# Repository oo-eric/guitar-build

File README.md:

# MIDI Guitar Build

A DIY guitar that doubles as a polyphonic MIDI controller. Six individual
single-string pickups feed a Teensy 4.0, which converts each string's vibration
into MIDI in real time — pitch, note on/off, and per-string pitch bend — using
the MPE (MIDI Polyphonic Expression) standard so every string lives on its own
channel and bends independently.

It's a _hybrid_ instrument: alongside the six hex pickups there's one standard
magnetic pickup, so it still plays and sounds like a normal guitar through an amp
while the digital side drives synths.

The electronics don't live in the guitar. The body carries pickups and a single
**13-pin (Roland GK standard) socket**; everything else — preamp, Teensy, MIDI
OUT, jacks — lives in a stompbox on the floor. The guitar end is entirely
passive.

## Status

**Phase 2 — 6-string expansion (in progress).**

- **Phase 1 (complete):** single-string proof of concept — pickup → buffer → ADC
  → onset detection → YIN pitch detection → MPE MIDI, end-to-end into a DAW.
- **Phase 2 (current):** modular firmware now runs all six strings. Single string
  is working end-to-end on the MCP6002 buffer (no battery); threshold calibration
  and per-string gain in progress. The **HexScope** app shows every string live
  on an iPhone, iPad or Mac, for checking wiring and comparing changes.
- **Phase 3 (started):** body and neck arrived 2026-08-08; the hex pickups are
  wired to the guitar's 13-pin socket but not yet connected to the preamp.
  Stomp box enclosure still to come. PCB designed and DRC-clean, waiting on a
  cable test before fabrication.
- **Future exploration:** an MPU-6050 accelerometer/gyro on the body or neck to
  turn physical gestures (tilt, shake, orientation) into MIDI CC.

See [`docs/plan.md`](docs/plan.md) for the full phased plan and parts list.

## Signal chain

```mermaid
flowchart LR
    subgraph G["Guitar (passive)"]
        S["Guitar string"] --> P["77HC hex pickup<br>×6"]
        M["Porter magnetic<br>pickup"]
        SW["Mode switch<br>Guitar / Mix / MIDI"]
        GJ["Guitar 1/4&quot; jack<br>(switched)"]
        M --> SW --> GJ
    end
    P --> K["13-pin GK cable<br>hex 1-6, magnetic 7, MIDI on/off 10"]
    GJ -- "no plug in" --> K
    SW -- "MIDI on/off" --> K
    subgraph BOX["Stomp box"]
        B["MCP6002 preamp<br>6ch, 46x, 3.3V from Teensy"]
        ADC["Teensy 4.0<br>A0-A5"]
        DSP["Onset → YIN pitch<br>→ MPE MIDI"]
        B --> ADC --> DSP
    end
    K --> B
    K --> J["1/4&quot; jack<br>(passive passthrough)"]
    DSP --> DIN["MIDI OUT<br>5-pin DIN"]
    DSP --> USB["USB-C"]
    GJ -- "plug in" --> AMP
    DIN --> SY["Hardware synth<br>(stage)"]
    USB --> C["Computer / DAW<br>(desk)"]
    J --> AMP["Amp"]
```

## Hardware

- **Teensy 4.0** — 600MHz ARM Cortex-M7, dual 12-bit ADC, built-in USB MIDI
- **Ubertar 77HC** single-string ("hexaphonic") pickups ×6
- **MCP6002** rail-to-rail op-amps ×3 (dual channel each = 6 buffer/gain stages),
  running on 3.3V from the Teensy — replaced the original TL072 + 9V battery
- **Porter Pickups** Filtertron-sized humbucker (neck), Boise-made. Goes out the
  guitar's own 1/4" jack when a plug is in it, otherwise down 13-pin pin 7 to the
  stomp box's jack. Wiring of record: [`docs/guitar_wiring.md`](docs/guitar_wiring.md)
- **Custom PCB** — 82 × 156 mm, 2-layer, all through-hole. Generated from
  scripts, not hand-drawn; see `hardware/` and `scripts/`
- Breadboard prototype today; the board is designed but not yet fabricated

Circuit of record: [`docs/buffer_circuit.md`](docs/buffer_circuit.md).
Stomp box design: [`docs/stompbox/`](docs/stompbox/README.md).

## Firmware

Arduino IDE + Teensyduino. Under `firmware/`:

- **`firmware/adc_test/`** — Phase 1 single-string sketch. Uses the Teensy Audio
  library + USB Audio for monitoring; YIN pitch detection.
- **`firmware/experiments/`** — sketches that are **not** part of the MIDI signal
  chain and aren't headed for the pedal. Currently the ILI9341 waveform display,
  parked as a bench tool. Its README records why.
- **`firmware/guitar_midi/`** — Phase 2 modular 6-string firmware. MIDI only
  (no USB Audio). Components:
  - `config.h` — all tunable constants (thresholds, sample rate, MIDI, per-string)
  - `adc_sampler.h/.cpp` — timer-driven 20kHz ADC sampling, 6 channels, per-channel ring buffers
  - `onset_detector.h/.cpp` — RMS-based per-string note on/off state machine
  - `pitch_detector.h/.cpp` — YIN pitch detection with hysteresis
  - `midi_output.h/.cpp` — MPE MIDI output with per-channel pitch bend tracking
  - `telemetry.h/.cpp` — per-string diagnostics sent as USB MIDI SysEx, for HexScope
  - `guitar_midi.ino` — orchestrator with staggered per-string pitch detection

### Flashing

1. Open the sketch in the Arduino IDE with Teensyduino installed.
2. Select **Tools → Board → Teensy 4.0**.
3. Set **Tools → USB Type → "Serial + MIDI"** (Phase 2). The Phase 1 `adc_test`
   sketch uses **"Serial + MIDI + Audio"**.
4. Upload. The Teensy enumerates as a USB MIDI device — add it as an MPE
   instrument in your DAW.

> **Apple Silicon without Rosetta** (macOS 27): use Teensyduino **1.62 or
> later**, which ships a native compiler. Arduino's bundled `ctags` is still
> Intel-only and breaks the `.ino` preprocessing step; see `AGENTS.md` for the
> current workaround.

> **Power note:** don't power the Teensy via VIN and USB at the same time without
> cutting the VIN-VUSB trace.

## Tooling

- **[`app/HexScope/`](app/HexScope/README.md)** — SwiftUI app for iPhone, iPad
  and Mac. Plug the Teensy into the phone and see each string's level, bias,
  pitch and waveform, with warnings for clipping, bad bias and swapped wires.
  Records captures you can compare before and after a change. It reads USB MIDI,
  because iOS can't open the Teensy's serial port.
- `scripts/teensy_serial.py` — serial reader for the Teensy CDC port
- `scripts/guitar_monitor.py` — terminal dashboard of onset / pitch output
- `scripts/gen_body_template.py`, `headstock_layout.py`, `headstock_preview.py`
  — body outline and headstock templates

## Repository layout

```text
firmware/        Teensy sketches
  adc_test/        Phase 1 single-string
  guitar_midi/     Phase 2 modular 6-string (the real one)
  experiments/     parked, not in the signal chain
app/HexScope/    iPhone / iPad / Mac diagnostics app (xcodegen project)
hardware/        KiCad schematic + PCB — GENERATED, do not hand-edit
docs/            build plan, hardware references, circuit + design notes
  stompbox/        enclosure: power, controls, pin map, prior art
scripts/         KiCad and template generators + host-side serial/debug tools
body/            body outline and headstock (OpenSCAD, printable template)
enclosure/       OpenSCAD models (pickup enclosure)
brainstorm/      concept sketches
output/          captured stage notes / logs
AGENTS.md        project instructions for the agent harness
```

`hardware/` is generated by `scripts/gen_kicad_schematic.py` and
`scripts/gen_kicad_pcb.py`. Regenerate in order — schematic →
`check_kicad_netlist.py` → PCB — and never hand-edit the KiCad files.

## Documentation

| Doc                                                              | What's in it                                                     |
| ---------------------------------------------------------------- | ---------------------------------------------------------------- |
| [`docs/plan.md`](docs/plan.md)                                   | Phased build plan, parts list, signal chain, technical notes     |
| [`docs/guitar_build.md`](docs/guitar_build.md)                   | Physical build specs and decisions                               |
| [`docs/guitar_wiring.md`](docs/guitar_wiring.md)                 | **Guitar wiring of record** — jacks, mode switch, grounding      |
| [`docs/guitar_wiring_diagram.md`](docs/guitar_wiring_diagram.md) | Bench sheet: diagram, wire list, meter and continuity checks     |
| [`docs/body_shape.md`](docs/body_shape.md)                       | Body outline design (Jazzmaster × Iceman hybrid)                 |
| [`docs/wood_comparison.md`](docs/wood_comparison.md)             | Body / neck / fretboard tonewood comparison                      |
| [`docs/pickup_selection.md`](docs/pickup_selection.md)           | Standard magnetic pickup selection (Porter Pickups)              |
| [`docs/buffer_circuit.md`](docs/buffer_circuit.md)               | **Circuit of record** — schematic, values, BOM, bring-up         |
| [`docs/stompbox/`](docs/stompbox/README.md)                      | Stomp box: I/O, power, controls, Teensy pin map, prior art       |
| [`docs/wip.md`](docs/wip.md)                                     | ⚠️ Historical Phase-1 breadboard wiring (TL072 + 9V). Superseded |
| [`docs/teensy-4.0.md`](docs/teensy-4.0.md)                       | Teensy 4.0 pinout / reference                                    |
| [`docs/ubertar-77hc-pickup.md`](docs/ubertar-77hc-pickup.md)     | Ubertar 77HC pickup reference                                    |

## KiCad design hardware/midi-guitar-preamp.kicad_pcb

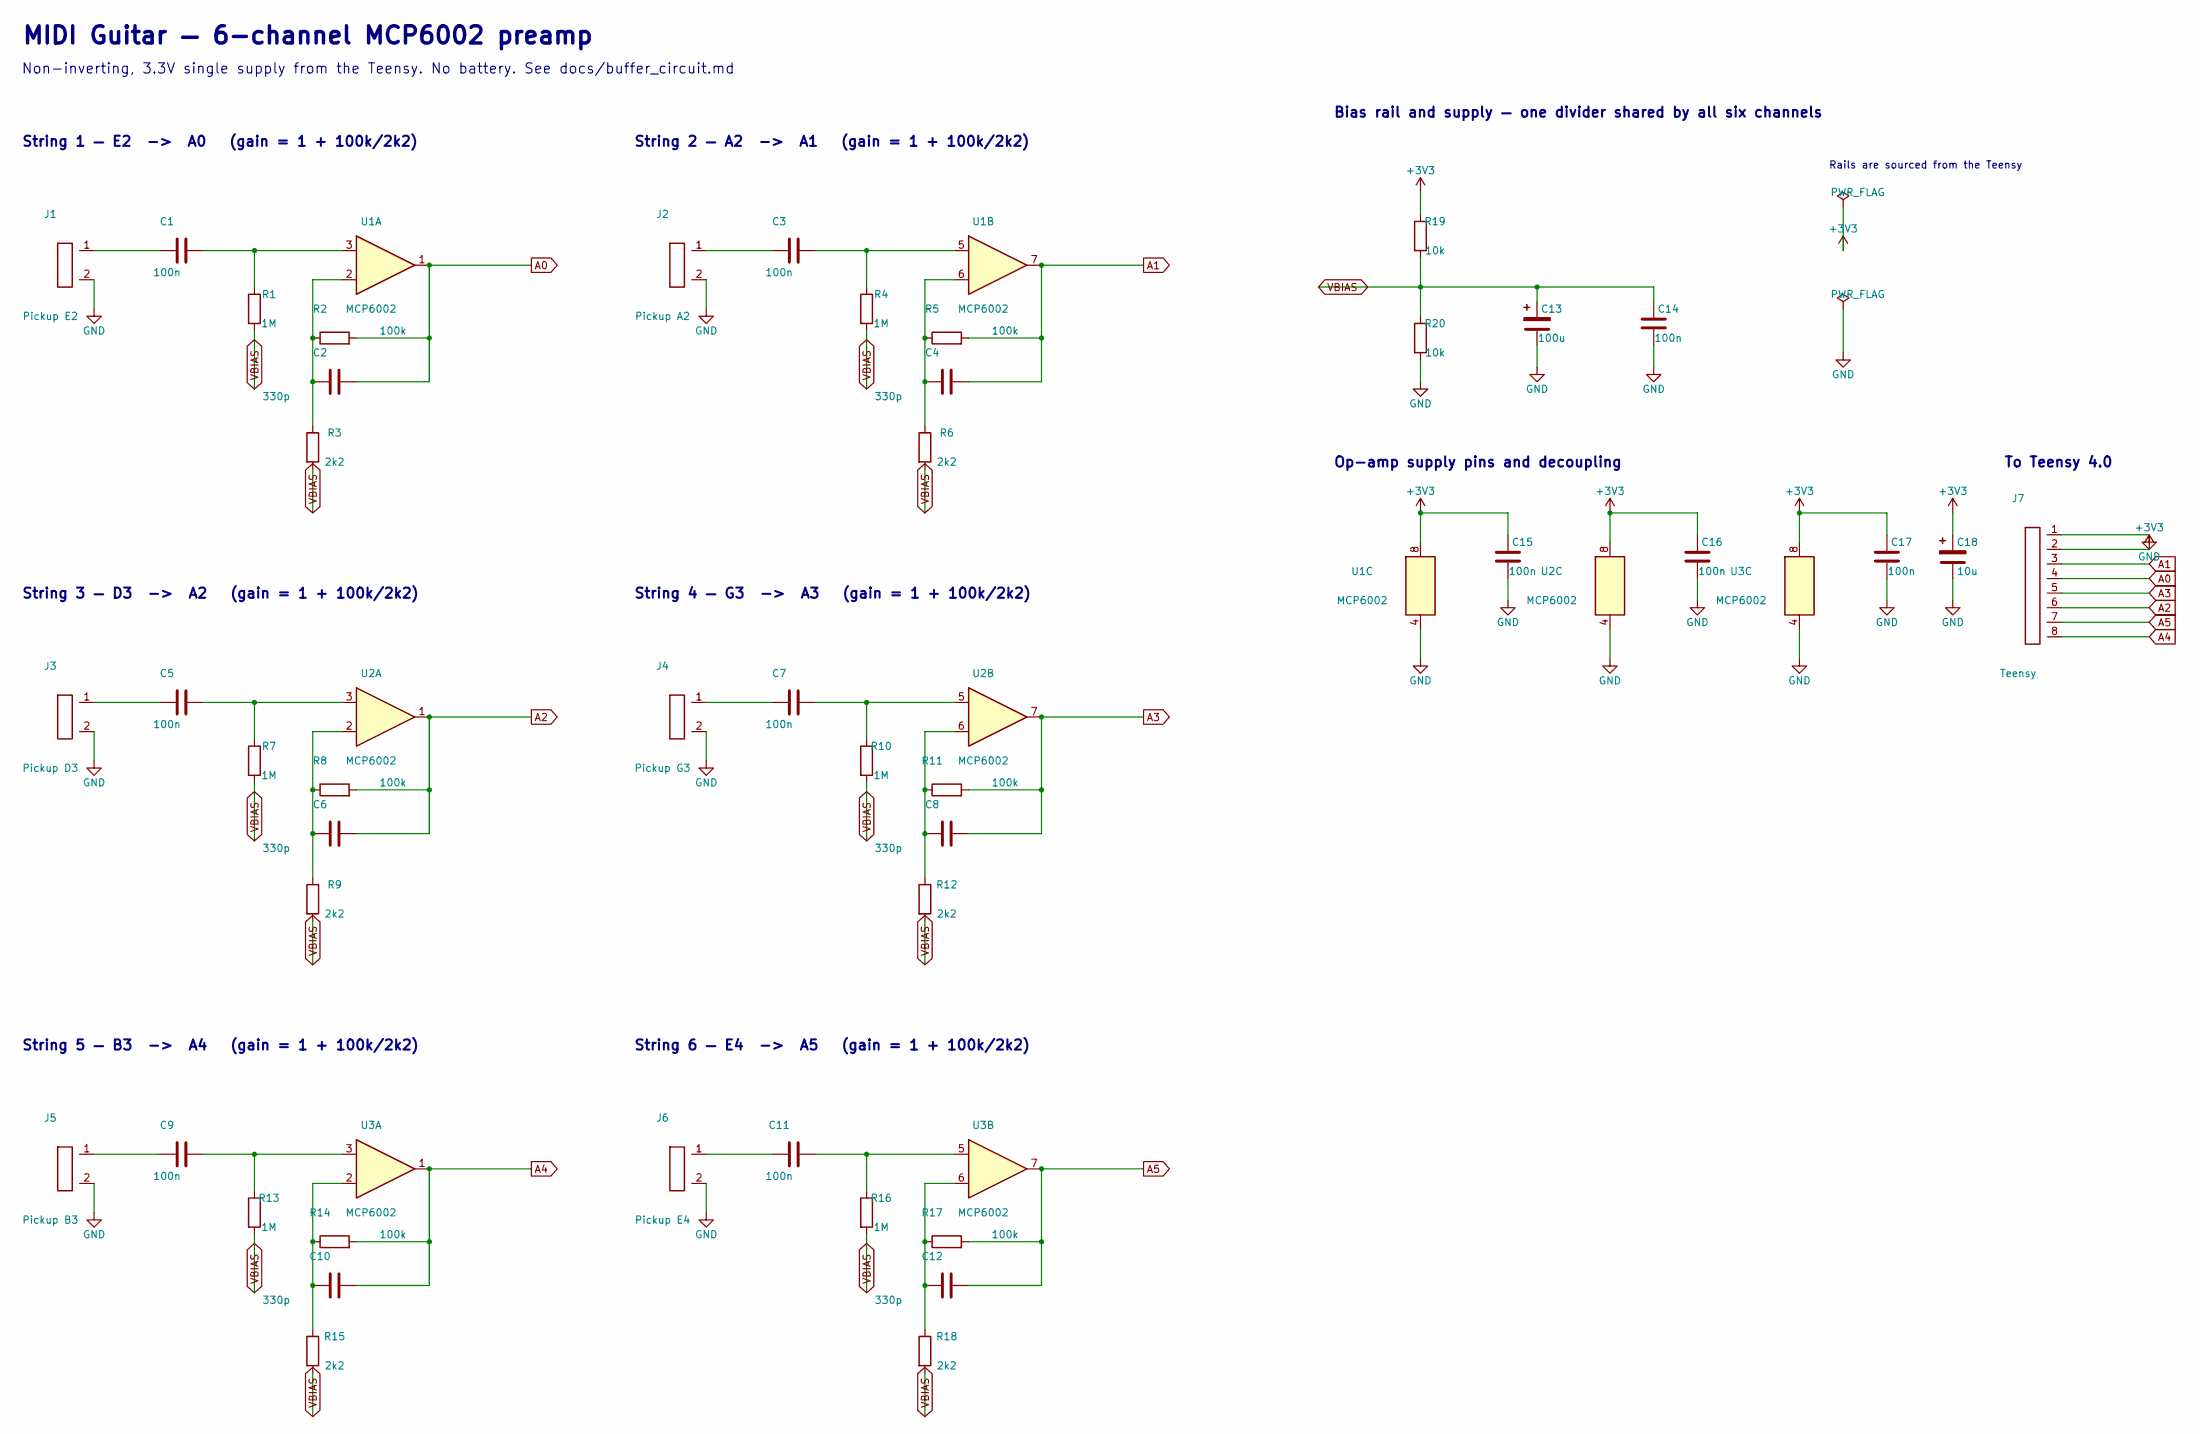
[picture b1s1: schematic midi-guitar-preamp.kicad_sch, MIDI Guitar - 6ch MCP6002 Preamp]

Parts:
C1, C3, C5, C7, C9, C11: 100n; C_Rect_L7.0mm_W2.5mm_P5.00mm
C2, C4, C6, C8, C10, C12: 330p; C_Disc_D5.0mm_W2.5mm_P5.00mm
C13: 100u; CP_Radial_D6.3mm_P2.50mm
C14, C15, C16, C17: 100n; C_Disc_D5.0mm_W2.5mm_P5.00mm
C18: 10u; CP_Radial_D6.3mm_P2.50mm
J1: Pickup E2; PinHeader_1x02_P2.54mm_Vertical
J2: Pickup A2; PinHeader_1x02_P2.54mm_Vertical
J3: Pickup D3; PinHeader_1x02_P2.54mm_Vertical
J4: Pickup G3; PinHeader_1x02_P2.54mm_Vertical
J5: Pickup B3; PinHeader_1x02_P2.54mm_Vertical
J6: Pickup E4; PinHeader_1x02_P2.54mm_Vertical
J7: Teensy; PinHeader_1x08_P2.54mm_Vertical
R1, R4, R7, R10, R13, R16: 1M; R_Axial_DIN0207_L6.3mm_D2.5mm_P7.62mm_Horizontal
R2, R5, R8, R11, R14, R17: 100k; R_Axial_DIN0207_L6.3mm_D2.5mm_P7.62mm_Horizontal
R3, R6, R9, R12, R15, R18: 2k2; R_Axial_DIN0207_L6.3mm_D2.5mm_P7.62mm_Horizontal
R19, R20: 10k; R_Axial_DIN0207_L6.3mm_D2.5mm_P7.62mm_Horizontal
U1, U2, U3: MCP6002; DIP-8_W7.62mm

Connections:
+3V3: C15.1, C16.1, C17.1, C18.1, J7.2, R19.1, U1.8 (VDD), U2.8 (VDD), U3.8 (VDD)
A0: C2.2, J7.4, R2.2, U1.1
A1: C4.2, J7.3, R5.2, U1.7
A2: C6.2, J7.6, R8.2, U2.1
A3: C8.2, J7.5, R11.2, U2.7
A4: C10.2, J7.8, R14.2, U3.1
A5: C12.2, J7.7, R17.2, U3.7
GND: C13.2, C14.2, C15.2, C16.2, C17.2, C18.2, J1.2, J2.2, J3.2, J4.2, J5.2, J6.2, J7.1, R20.2, U1.4 (VSS), U2.4 (VSS), U3.4 (VSS)
unnamed: C1.1, J1.1
unnamed: C3.1, J2.1
unnamed: C5.1, J3.1
unnamed: C7.1, J4.1
unnamed: C9.1, J5.1
unnamed: C11.1, J6.1
unnamed: C1.2, R1.1, U1.3 (+)
unnamed: C2.1, R2.1, R3.1, U1.2 (-)
unnamed: C3.2, R4.1, U1.5 (+)
unnamed: C4.1, R5.1, R6.1, U1.6 (-)
unnamed: C5.2, R7.1, U2.3 (+)
unnamed: C6.1, R8.1, R9.1, U2.2 (-)
unnamed: C7.2, R10.1, U2.5 (+)
unnamed: C8.1, R11.1, R12.1, U2.6 (-)
unnamed: C9.2, R13.1, U3.3 (+)
unnamed: C10.1, R14.1, R15.1, U3.2 (-)
unnamed: C11.2, R16.1, U3.5 (+)
unnamed: C12.1, R17.1, R18.1, U3.6 (-)
VBIAS: C13.1, C14.1, R1.2, R3.2, R4.2, R6.2, R7.2, R9.2, R10.2, R12.2, R13.2, R15.2, R16.2, R18.2, R19.2, R20.1

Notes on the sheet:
MIDI Guitar — 6-channel MCP6002 preamp
Non-inverting, 3.3V single supply from the Teensy. No battery. See docs/buffer_circuit.md
String 1 — E2 -> A0 (gain = 1 + 100k/2k2)
String 2 — A2 -> A1 (gain = 1 + 100k/2k2)
String 3 — D3 -> A2 (gain = 1 + 100k/2k2)
String 4 — G3 -> A3 (gain = 1 + 100k/2k2)
String 5 — B3 -> A4 (gain = 1 + 100k/2k2)
String 6 — E4 -> A5 (gain = 1 + 100k/2k2)
Bias rail and supply — one divider shared by all six channels
Op-amp supply pins and decoupling
Rails are sourced from the Teensy
To Teensy 4.0

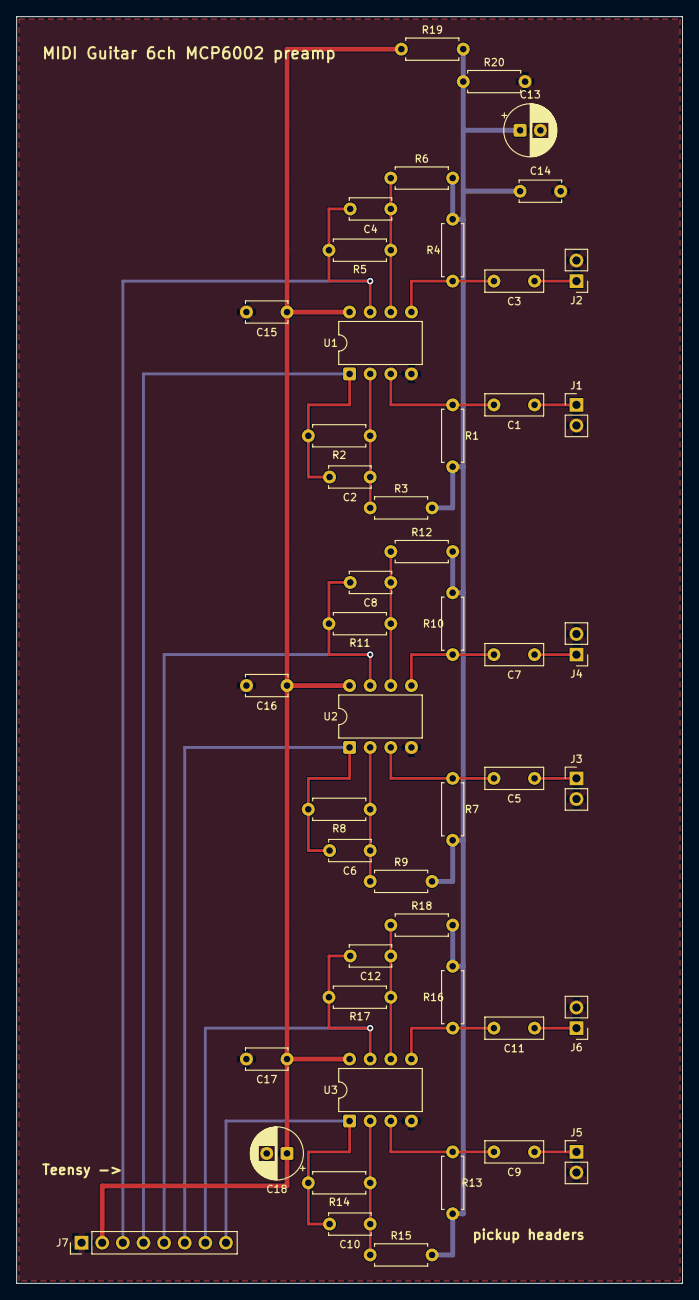
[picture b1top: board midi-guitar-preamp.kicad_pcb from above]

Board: 2 copper layers, 82.0 x 156.0 mm, 48 parts (0 on the bottom side), 27 nets.

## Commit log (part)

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2026-02-19 add first pass at plan
2026-02-28 initial plan
2026-02-28 first pass
2026-02-28 built
2026-02-28 add schematic
2026-03-13 teensy 4.0
2026-03-13 Working single pickup
2026-03-13 working midi in
2026-03-13 update plan, guitar build
2026-03-14 combined audio + midi stream for single pickup
2026-03-14 update docs
2026-03-15 add visualization, slow ~120 ms
2026-03-15 work in progress with sprites, on hold until spi pins are wired to the bottom
2026-03-15 refine pitch jumps, signal thresholds
2026-03-15 wip on 6 sixstrings
2026-03-15 debugging
2026-05-07 no 9v battery
2026-06-01 wood info
2026-06-01 build locked
2026-06-04 cleanup
2026-06-07 ubertar pickup specs update
2026-06-09 no rear rout
